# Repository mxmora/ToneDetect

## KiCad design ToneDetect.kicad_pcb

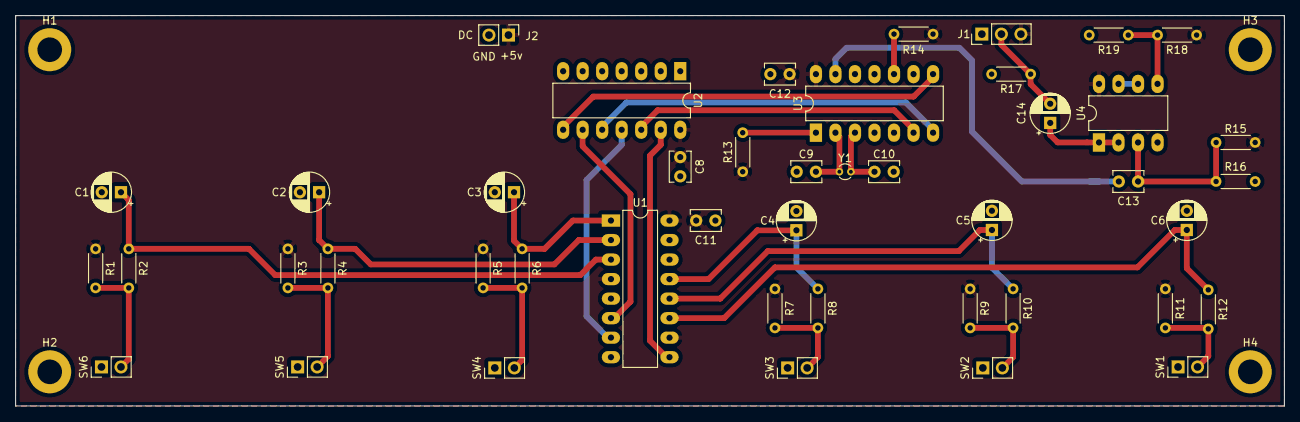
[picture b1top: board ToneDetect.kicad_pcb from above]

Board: 2 copper layers, 165.1 x 50.8 mm, 49 parts (0 on the bottom side), 30 nets.

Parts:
C1, C2, C3, C4, C5, C6, C14: 10uf; CP_Radial_D5.0mm_P2.50mm
C8, C11, C12: 100nf; C_Disc_D3.8mm_W2.6mm_P2.50mm
C9, C10: 20pf; C_Disc_D3.8mm_W2.6mm_P2.50mm
C13: .1uf; C_Disc_D3.8mm_W2.6mm_P2.50mm
H1, H2, H3, H4: M; MountingHole_3.2mm_M3_DIN965_Pad
J1: XLR3; PinHeader_1x03_P2.54mm_Vertical
J2: DC; PinHeader_1x02_P2.54mm_Vertical
R1, R3, R5, R7, R9, R11, R13, R14, R17, R18, R19: 10k; R_Axial_DIN0204_L3.6mm_D1.6mm_P5.08mm_Horizontal
R2, R4, R6, R8, R10, R12: 1k; R_Axial_DIN0204_L3.6mm_D1.6mm_P5.08mm_Horizontal
R15, R16: 1m; R_Axial_DIN0204_L3.6mm_D1.6mm_P5.08mm_Horizontal
SW1, SW2, SW3, SW4, SW5, SW6: SW_SPST; PinHeader_1x02_P2.54mm_Vertical
U1: 74LS148; DIP-16_W7.62mm_LongPads
U2: 74HCT04; DIP-14_W7.62mm_LongPads
U3: HT9200B; DIP-14_W7.62mm_LongPads
U4: LM358; DIP-8_W7.62mm_LongPads
Y1: 3.5795mHz; Crystal_DS10_D1.0mm_L4.3mm_Vertical

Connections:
+5V: C8.1, C11.2, C12.1, J1.3, J2.1, R1.1, R3.1, R5.1, R7.1, R9.1, R11.1, R13.1, R14.1, R15.1, R18.1, U1.4, U1.10, U1.16, U2.14, U3.14, U4.8
GND: C1.2, C2.2, C3.2, C4.2, C5.2, C6.2, C8.2, C9.2, C10.2, C11.1, C12.2, H1.1, H2.1, H3.1, H4.1, J1.1, J2.2, R16.2, R17.2, R19.2, SW1.1, SW2.1, SW3.1, SW4.1, SW5.1, SW6.1, U1.5, U1.8, U2.1, U2.3, U2.5, U2.7, U3.4, U3.9, U4.4
unnamed: C1.1, R2.1, U1.3
unnamed: C2.1, R4.1, U1.2
unnamed: C3.1, R6.1, U1.1
unnamed: C4.1, R8.1, U1.13
unnamed: C5.1, R10.1, U1.12
unnamed: C6.1, R12.1, U1.11
unnamed: C9.1, U3.2, Y1.1
unnamed: C10.1, U3.3, Y1.2
unnamed: C13.1, R15.2, R16.1, U4.3
unnamed: C13.2, U3.13
unnamed: C14.1, U4.1, U4.2
unnamed: C14.2, J1.2, R17.1
unnamed: R1.2, R2.2, SW6.2
unnamed: R3.2, R4.2, SW5.2
unnamed: R5.2, R6.2, SW4.2
unnamed: R7.2, R8.2, SW3.2
unnamed: R9.2, R10.2, SW2.2
unnamed: R11.2, R12.2, SW1.2
unnamed: R13.2, U3.1
unnamed: R14.2, U3.10
unnamed: R18.2, R19.1, U4.5
unnamed: U1.6, U2.9
unnamed: U1.7, U2.11
unnamed: U1.9, U2.13
unnamed: U2.8, U3.8
unnamed: U2.10, U3.7
unnamed: U2.12, U3.6
unnamed: U4.6, U4.7

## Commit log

2019-07-24 First commit of files
2019-07-25 tweaks to schematic and layout
2019-07-26 tweak design
2019-08-02 remove a hex inverter and fix up circuit
